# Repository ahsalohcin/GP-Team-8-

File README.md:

# Grand PrIEEE (senior year of undergrad, 2016-2017)

Led a team of 5 for IEEE-sponsored competition for designing a line-following RC car from scratch.

## Competition videos: 
* UC San Diego (3rd place): https://www.youtube.com/watch?v=oybaJ443wYY 
* UC Davis (4th place):  https://www.youtube.com/watch?v=VBZ95nvLsOQ& 

## Overview: 
* 1/12 scale RC car + custom PCB
* __Microcontroller__: Teensy (Arduino based)
* __Sensors__: line camera and hall effect speed sensor
* __Actuators__: servo and brushed DC motor (with custom designed motor driver circuit)
* __Controllers__: PD for steering, PI for speed

## Skills learned: 
* Project management
* Design and integration (mechanical, electrical, and software)
* PCB layout
* Control design and tuning

## Main code: 
https://github.com/ahsalohcin/GP-Team-8-/blob/master/Code_5_7/GP_teensy/GP_teensy.ino

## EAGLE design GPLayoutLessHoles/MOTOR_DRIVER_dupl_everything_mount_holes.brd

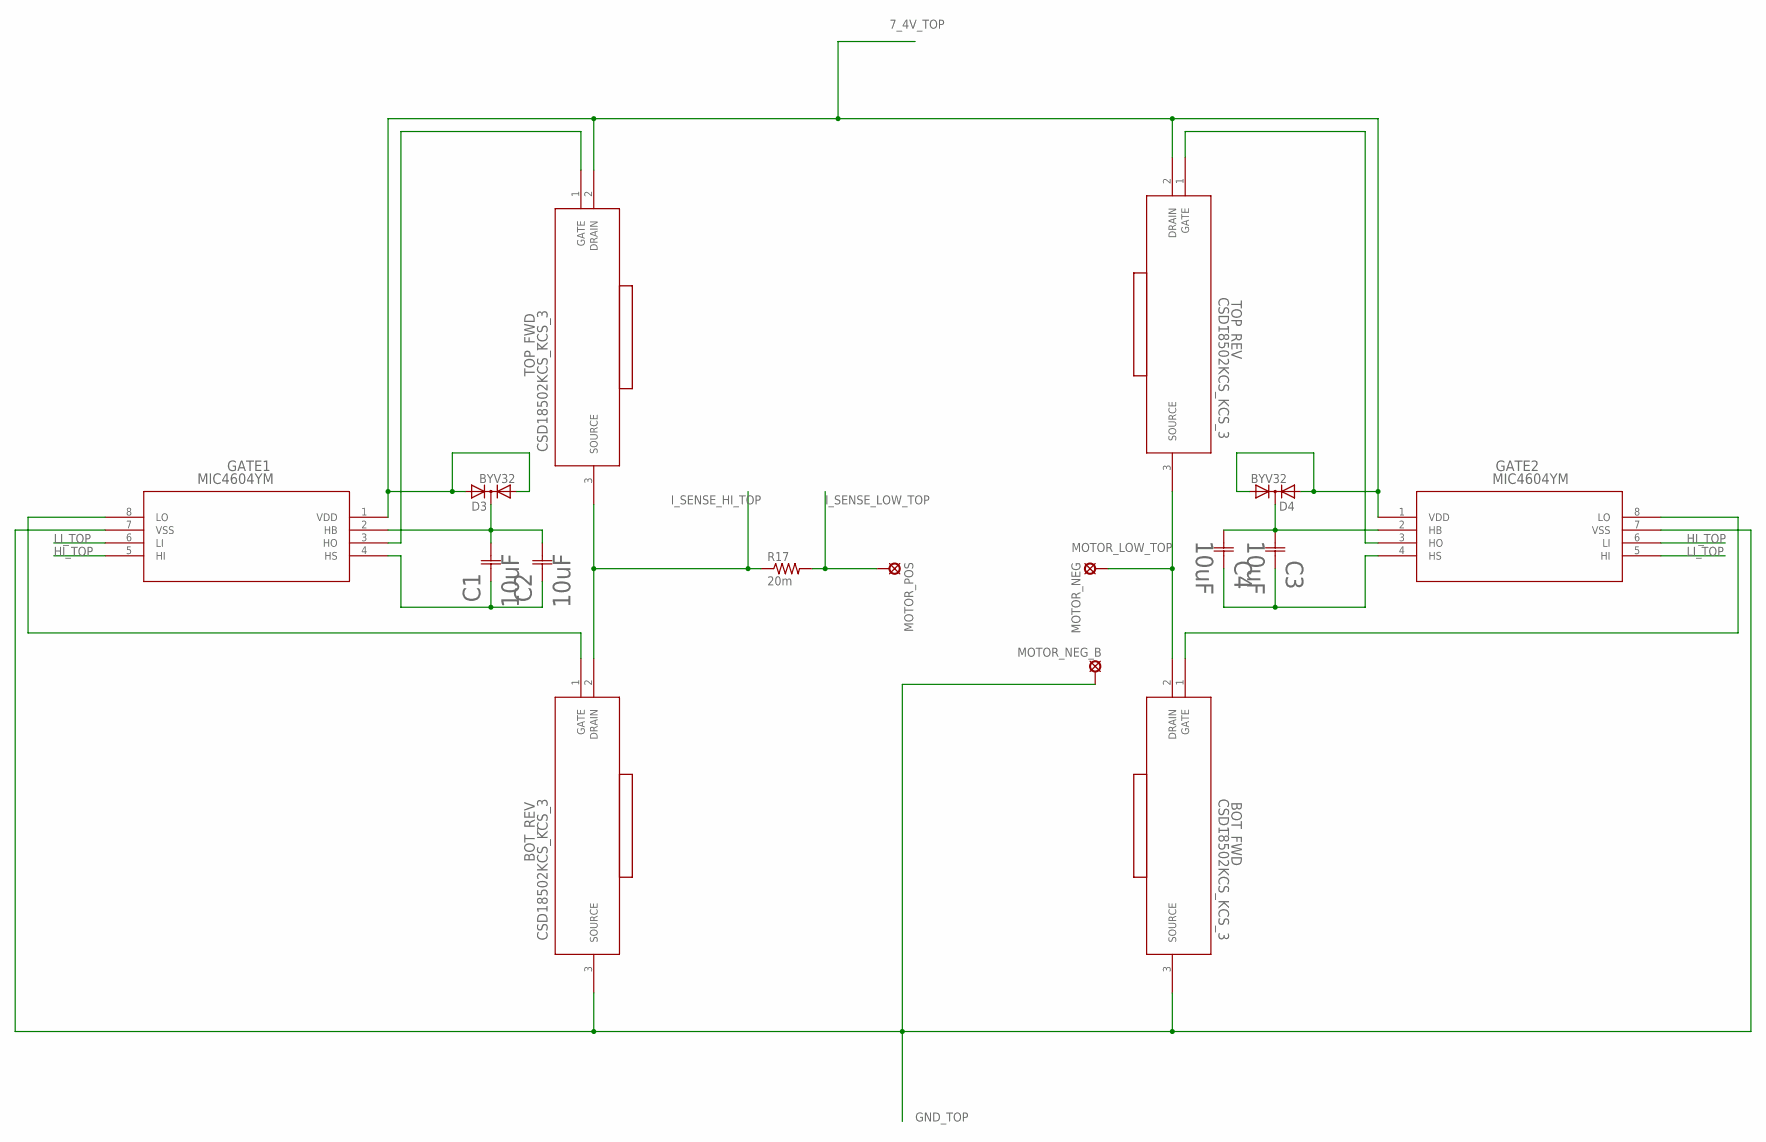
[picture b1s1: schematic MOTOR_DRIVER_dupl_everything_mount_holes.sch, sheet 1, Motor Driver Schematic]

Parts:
BOT_FWD: CSD18502KCS_KCS_3; KCS3
BOT_REV: CSD18502KCS_KCS_3; KCS3
C1, C2, C3, C4: 10uF; CAP_EEE_B
D3, D4: BYV32; TO220ABS
GATE1, GATE2: MIC4604YM; SOIC-8_M
MOTOR_NEG: SE14
MOTOR_NEG_B: SE14
MOTOR_POS: SE14
R17: 20m; R2512
TOP_FWD: CSD18502KCS_KCS_3; KCS3
TOP_REV: CSD18502KCS_KCS_3; KCS3
U$2, U$4, U$5, U$6: HEATSINK

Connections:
7_4V_TOP: D3.A1, D3.A2, D4.A1, D4.A2, GATE1.1 (VDD), GATE2.1 (VDD), TOP_FWD.2 (DRAIN), TOP_REV.2 (DRAIN); also elsewhere on the board
GND_TOP: BOT_FWD.3 (SOURCE), BOT_REV.3 (SOURCE), GATE1.7 (VSS), GATE2.7 (VSS), MOTOR_NEG_B.MP; also elsewhere on the board
HI_TOP: GATE1.5 (HI), GATE2.6 (LI); also elsewhere on the board
I_SENSE_HI_TOP: BOT_REV.2 (DRAIN), R17.1, TOP_FWD.3 (SOURCE); also elsewhere on the board
I_SENSE_LOW_TOP: MOTOR_POS.MP, R17.2; also elsewhere on the board
LI_TOP: GATE1.6 (LI), GATE2.5 (HI); also elsewhere on the board
MOTOR_LOW_TOP: BOT_FWD.2 (DRAIN), MOTOR_NEG.MP, TOP_REV.3 (SOURCE); also elsewhere on the board
unnamed: BOT_REV.1 (GATE), GATE1.8 (LO)
unnamed: GATE1.3 (HO), TOP_FWD.1 (GATE)
unnamed: C1.1, C2.1, GATE1.4 (HS)
unnamed: C1.2, C2.2, D3.C, GATE1.2 (HB)
unnamed: BOT_FWD.1 (GATE), GATE2.8 (LO)
unnamed: GATE2.3 (HO), TOP_REV.1 (GATE)
unnamed: C3.1, C4.1, GATE2.4 (HS)
unnamed: C3.2, C4.2, D4.C, GATE2.2 (HB)

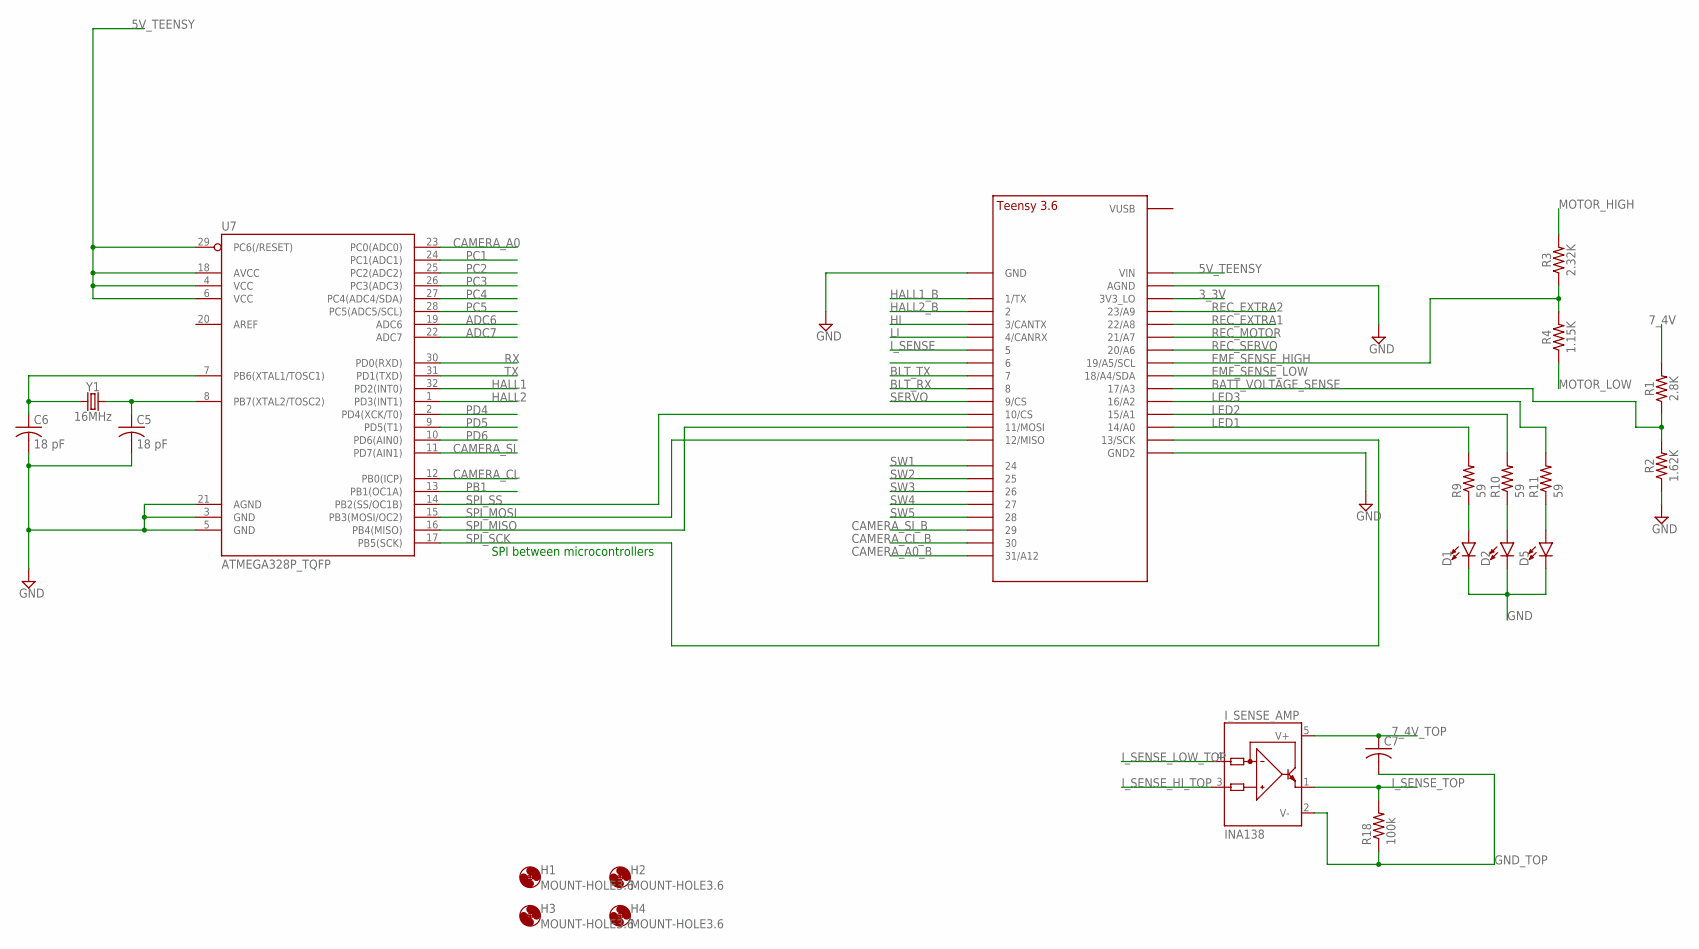
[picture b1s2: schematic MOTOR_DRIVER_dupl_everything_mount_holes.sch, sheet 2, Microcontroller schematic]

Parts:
C5, C6: 18 pF; C0603
C7: C-USC0603; C0603
D1, D2, D5: LED0603; LED-0603
H1, H2, H3, H4: MOUNT-HOLE3.6; 3,6
I_SENSE_AMP: INA138; SOT23-5
R1: 2.8K; 0805; MANUFACTURER_PART_NUMBER RC0805FR-072K8L; DIGIKEY_PART_NUMBER 311-2.80KCRCT-ND
R2: 1.62K; 0805; MANUFACTURER_PART_NUMBER RC0805FR-071K62L; DIGIKEY_PART_NUMBER 311-1.62KCRCT-ND
R3: 2.32K; 0805; MANUFACTURER_PART_NUMBER RC0805FR-072K32L; DIGIKEY_PART_NUMBER 311-2.32KCRCT-ND
R4: 1.15K; 0805; MANUFACTURER_PART_NUMBER RC0805FR-071K15L; DIGIKEY_PART_NUMBER 311-1.15KCRCT-ND
R9, R10, R11: 59; R0805
R18: 100k; R0603
U7: ATMEGA328P_TQFP; TQFP32-08; MANUFACTURER_PART_NUMBER ATMEGA328PB-AU; DIGIKEY_PART_NUMBER ATMEGA328PB-AU-ND
U$1: TEENSY_3.5/3.6_FEWER; TEENSY_3.5/3.6_BASIC_FEWER_PIN; MANUFACTURER_PART_NUMBER DEV-14055; DIGIKEY_PART_NUMBER 1568-1443-ND
Y1: 16MHz; HC49US; MANUFACTURER_PART_NUMBER 9C-16.000MBBK-T; DIGIKEY_PART_NUMBER 887-2425-1-ND

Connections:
3_3V: U$1.3V3_LO; also elsewhere on the board
5V_TEENSY: U7.4 (VCC), U7.6 (VCC), U7.18 (AVCC), U7.29 (PC6(/RESET)), U$1.VIN; also elsewhere on the board
7_4V: R1.2; also elsewhere on the board
7_4V_TOP: C7.1, I_SENSE_AMP.5 (V+); also elsewhere on the board
ADC6: U7.19 (ADC6); also elsewhere on the board
ADC7: U7.22 (ADC7); also elsewhere on the board
BATT_VOLTAGE_SENSE: R1.1, R2.2, U$1.17/A3
BLT_RX: U$1.8; also elsewhere on the board
BLT_TX: U$1.7; also elsewhere on the board
CAMERA_A0: U7.23 (PC0(ADC0)); also elsewhere on the board
CAMERA_A0_B: U$1.31/A12; also elsewhere on the board
CAMERA_CL: U7.12 (PB0(ICP)); also elsewhere on the board
CAMERA_CL_B: U$1.30; also elsewhere on the board
CAMERA_SI: U7.11 (PD7(AIN1)); also elsewhere on the board
CAMERA_SI_B: U$1.29; also elsewhere on the board
EMF_SENSE_HIGH: R3.1, R4.2, U$1.19/A5/SCL
EMF_SENSE_LOW: U$1.18/A4/SDA; also elsewhere on the board
GND: C5.2, C6.2, D1.C, D2.C, D5.C, R2.1, U7.3 (GND), U7.5 (GND), U7.21 (AGND), U$1.AGND, U$1.GND, U$1.GND2; also elsewhere on the board
GND_TOP: C7.2, I_SENSE_AMP.2 (V-), R18.1; also elsewhere on the board
HALL1: U7.32 (PD2(INT0)); also elsewhere on the board
HALL1_B: U$1.1/TX; also elsewhere on the board
HALL2: U7.1 (PD3(INT1)); also elsewhere on the board
HALL2_B: U$1.2; also elsewhere on the board
HI: U$1.3/CANTX; also elsewhere on the board
I_SENSE: U$1.5; also elsewhere on the board
I_SENSE_HI_TOP: I_SENSE_AMP.3 (IN+); also elsewhere on the board
I_SENSE_LOW_TOP: I_SENSE_AMP.4 (IN-); also elsewhere on the board
I_SENSE_TOP: I_SENSE_AMP.1 (OUT), R18.2; also elsewhere on the board
LED1: R9.2, U$1.14/A0
LED2: R10.2, U$1.15/A1
LED3: R11.2, U$1.16/A2
LI: U$1.4/CANRX; also elsewhere on the board
LI2: U$1.6
MOTOR_HIGH: R3.2; also elsewhere on the board
MOTOR_LOW: R4.1; also elsewhere on the board
unnamed: C6.1, U7.7 (PB6(XTAL1/TOSC1)), Y1.1
unnamed: C5.1, U7.8 (PB7(XTAL2/TOSC2)), Y1.2
unnamed: D1.A, R9.1
unnamed: D2.A, R10.1
unnamed: D5.A, R11.1
PB1: U7.13 (PB1(OC1A)); also elsewhere on the board
PC1: U7.24 (PC1(ADC1)); also elsewhere on the board
PC2: U7.25 (PC2(ADC2)); also elsewhere on the board
PC3: U7.26 (PC3(ADC3)); also elsewhere on the board
PC4: U7.27 (PC4(ADC4/SDA)); also elsewhere on the board
PC5: U7.28 (PC5(ADC5/SCL)); also elsewhere on the board
PD4: U7.2 (PD4(XCK/T0)); also elsewhere on the board
PD5: U7.9 (PD5(T1)); also elsewhere on the board
PD6: U7.10 (PD6(AIN0))
REC_EXTRA1: U$1.22/A8; also elsewhere on the board
REC_EXTRA2: U$1.23/A9; also elsewhere on the board
REC_MOTOR: U$1.21/A7; also elsewhere on the board
REC_SERVO: U$1.20/A6; also elsewhere on the board
RX: U7.30 (PD0(RXD)); also elsewhere on the board
SERVO: U$1.9/CS; also elsewhere on the board
SPI_MISO: U7.16 (PB4(MISO)), U$1.11/MOSI
SPI_MOSI: U7.15 (PB3(MOSI/OC2)), U$1.12/MISO
SPI_SCK: U7.17 (PB5(SCK)), U$1.13/SCK
SPI_SS: U7.14 (PB2(SS/OC1B)), U$1.10/CS
SW1: U$1.24; also elsewhere on the board
SW2: U$1.25; also elsewhere on the board
SW3: U$1.26; also elsewhere on the board
SW4: U$1.27; also elsewhere on the board
SW5: U$1.28
TX: U7.31 (PD1(TXD)); also elsewhere on the board

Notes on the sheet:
SPI between microcontrollers

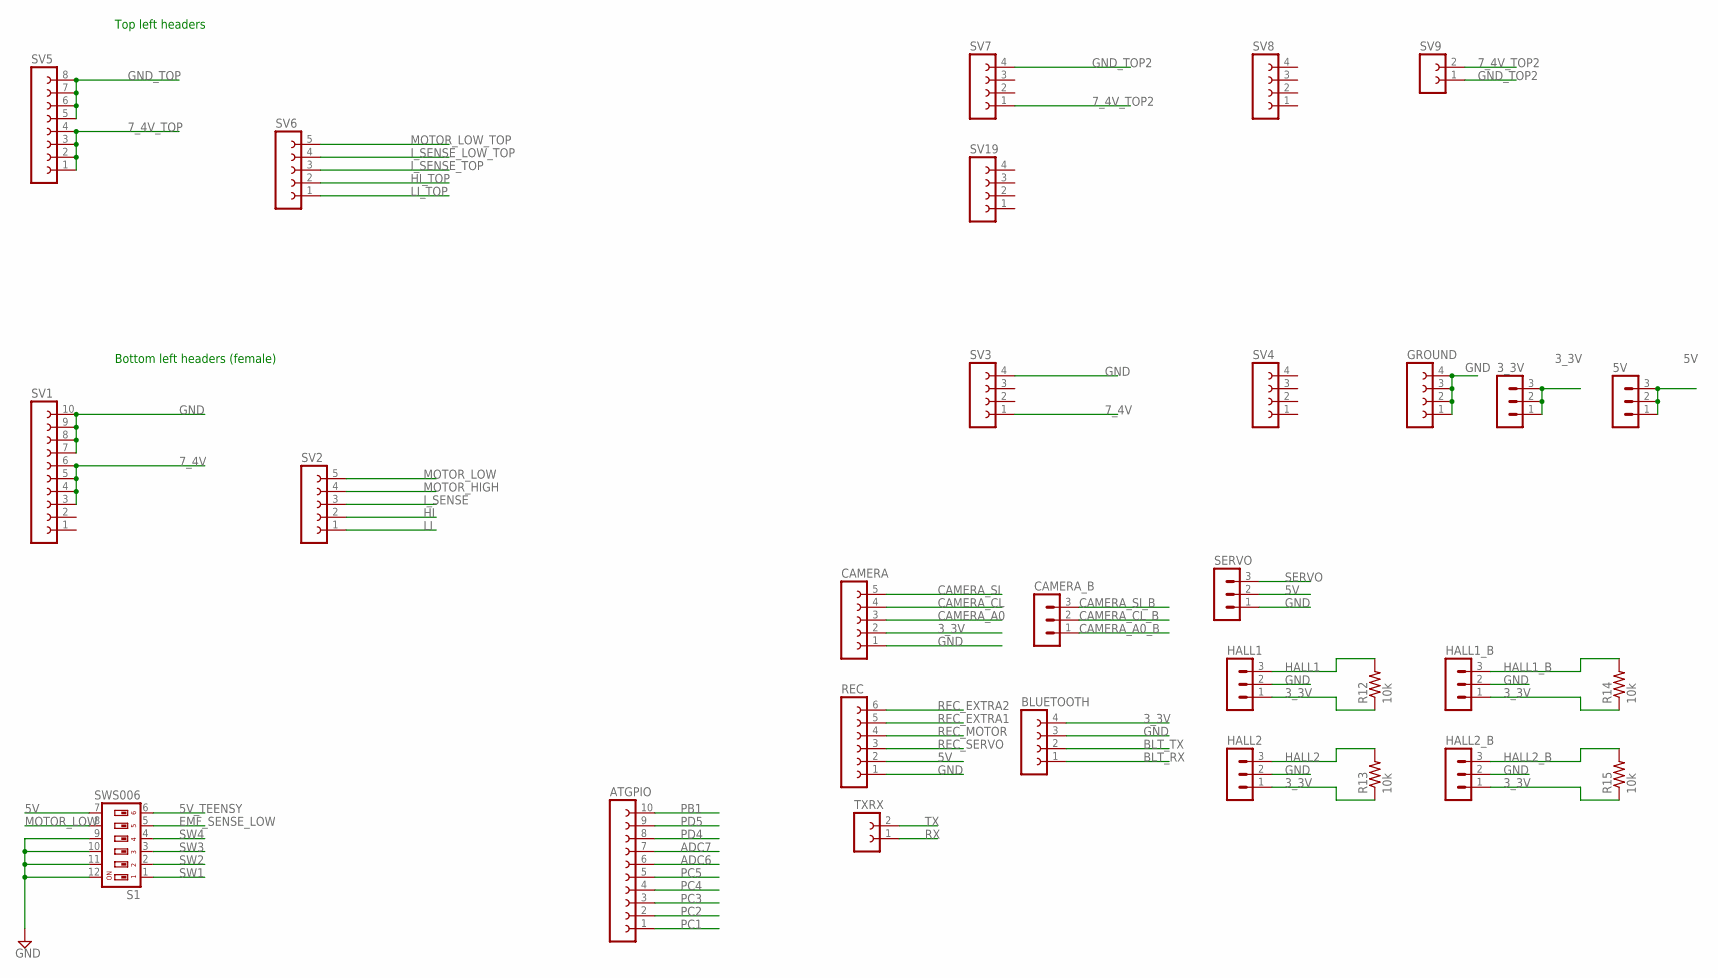
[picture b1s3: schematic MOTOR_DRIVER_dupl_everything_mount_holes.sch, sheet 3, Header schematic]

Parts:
3_3V, 5V: MA03-1
ATGPIO: FE10-1; FE10
BLUETOOTH: FE04-1; MANUFACTURER_PART_NUMBER HC-06
CAMERA: FE05-1; MANUFACTURER_PART_NUMBER 28317; DIGIKEY_PART_NUMBER 28317-ND
CAMERA_B: MA03-1; MANUFACTURER_PART_NUMBER 28317; DIGIKEY_PART_NUMBER 28317-ND
GROUND: FE04-1
HALL1, HALL1_B, HALL2, HALL2_B: MA03-1; MANUFACTURER_PART_NUMBER US1881LUA-AAA-000-BU; DIGIKEY_PART_NUMBER US1881LUA-AAA-000-BU-ND
R12, R13, R14, R15: 10k; R0603
REC: FE06-1; FE06
S1: SWS006; SMS-006; MANUFACTURER_PART_NUMBER 219-6MST; DIGIKEY_PART_NUMBER CT2196MST-ND
SERVO: MA03-1; MANUFACTURER_PART_NUMBER TS-P12S
SV1: FE10-1; FE10
SV2, SV6: FE05-1
SV3, SV4, SV7, SV8, SV19: FE04-1
SV5: FE08-1; FE08
SV9: FE02-1
TXRX: FE02-1

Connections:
3_3V: 3_3V.1, 3_3V.2, 3_3V.3, BLUETOOTH.4, CAMERA.2, HALL1.1, HALL1_B.1, HALL2.1, HALL2_B.1, R12.1, R13.1, R14.1, R15.1; also elsewhere on the board
5V: 5V.1, 5V.2, 5V.3, REC.2, S1.7, SERVO.2; also elsewhere on the board
5V_TEENSY: S1.6; also elsewhere on the board
7_4V: SV1.3, SV1.4, SV1.5, SV1.6, SV3.1; also elsewhere on the board
7_4V_TOP: SV5.1, SV5.2, SV5.3, SV5.4; also elsewhere on the board
7_4V_TOP2: SV7.1, SV9.2; also elsewhere on the board
ADC6: ATGPIO.6; also elsewhere on the board
ADC7: ATGPIO.7; also elsewhere on the board
BLT_RX: BLUETOOTH.1; also elsewhere on the board
BLT_TX: BLUETOOTH.2; also elsewhere on the board
CAMERA_A0: CAMERA.3; also elsewhere on the board
CAMERA_A0_B: CAMERA_B.1; also elsewhere on the board
CAMERA_CL: CAMERA.4; also elsewhere on the board
CAMERA_CL_B: CAMERA_B.2; also elsewhere on the board
CAMERA_SI: CAMERA.5; also elsewhere on the board
CAMERA_SI_B: CAMERA_B.3; also elsewhere on the board
EMF_SENSE_LOW: S1.5; also elsewhere on the board
GND: BLUETOOTH.3, CAMERA.1, GROUND.1, GROUND.2, GROUND.3, GROUND.4, HALL1.2, HALL1_B.2, HALL2.2, HALL2_B.2, REC.1, S1.9, S1.10, S1.11, S1.12, SERVO.1, SV1.7, SV1.8, SV1.9, SV1.10, SV3.4; also elsewhere on the board
GND_TOP: SV5.5, SV5.6, SV5.7, SV5.8; also elsewhere on the board
GND_TOP2: SV7.4, SV9.1; also elsewhere on the board
HALL1: HALL1.3, R12.2; also elsewhere on the board
HALL1_B: HALL1_B.3, R14.2; also elsewhere on the board
HALL2: HALL2.3, R13.2; also elsewhere on the board
HALL2_B: HALL2_B.3, R15.2; also elsewhere on the board
HI: SV2.2; also elsewhere on the board
HI_TOP: SV6.2; also elsewhere on the board
I_SENSE: SV2.3; also elsewhere on the board
I_SENSE_LOW_TOP: SV6.4; also elsewhere on the board
I_SENSE_TOP: SV6.3; also elsewhere on the board
LI: SV2.1; also elsewhere on the board
LI_TOP: SV6.1; also elsewhere on the board
MOTOR_HIGH: SV2.4; also elsewhere on the board
MOTOR_LOW: S1.8, SV2.5; also elsewhere on the board
MOTOR_LOW_TOP: SV6.5; also elsewhere on the board
PB1: ATGPIO.10; also elsewhere on the board
PC1: ATGPIO.1; also elsewhere on the board
PC2: ATGPIO.2; also elsewhere on the board
PC3: ATGPIO.3; also elsewhere on the board
PC4: ATGPIO.4; also elsewhere on the board
PC5: ATGPIO.5; also elsewhere on the board
PD4: ATGPIO.8; also elsewhere on the board
PD5: ATGPIO.9; also elsewhere on the board
REC_EXTRA1: REC.5; also elsewhere on the board
REC_EXTRA2: REC.6; also elsewhere on the board
REC_MOTOR: REC.4; also elsewhere on the board
REC_SERVO: REC.3; also elsewhere on the board
RX: TXRX.1; also elsewhere on the board
SERVO: SERVO.3; also elsewhere on the board
SW1: S1.1; also elsewhere on the board
SW2: S1.2; also elsewhere on the board
SW3: S1.3; also elsewhere on the board
SW4: S1.4; also elsewhere on the board
TX: TXRX.2; also elsewhere on the board

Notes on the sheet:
Bottom left headers (female)
Top left headers

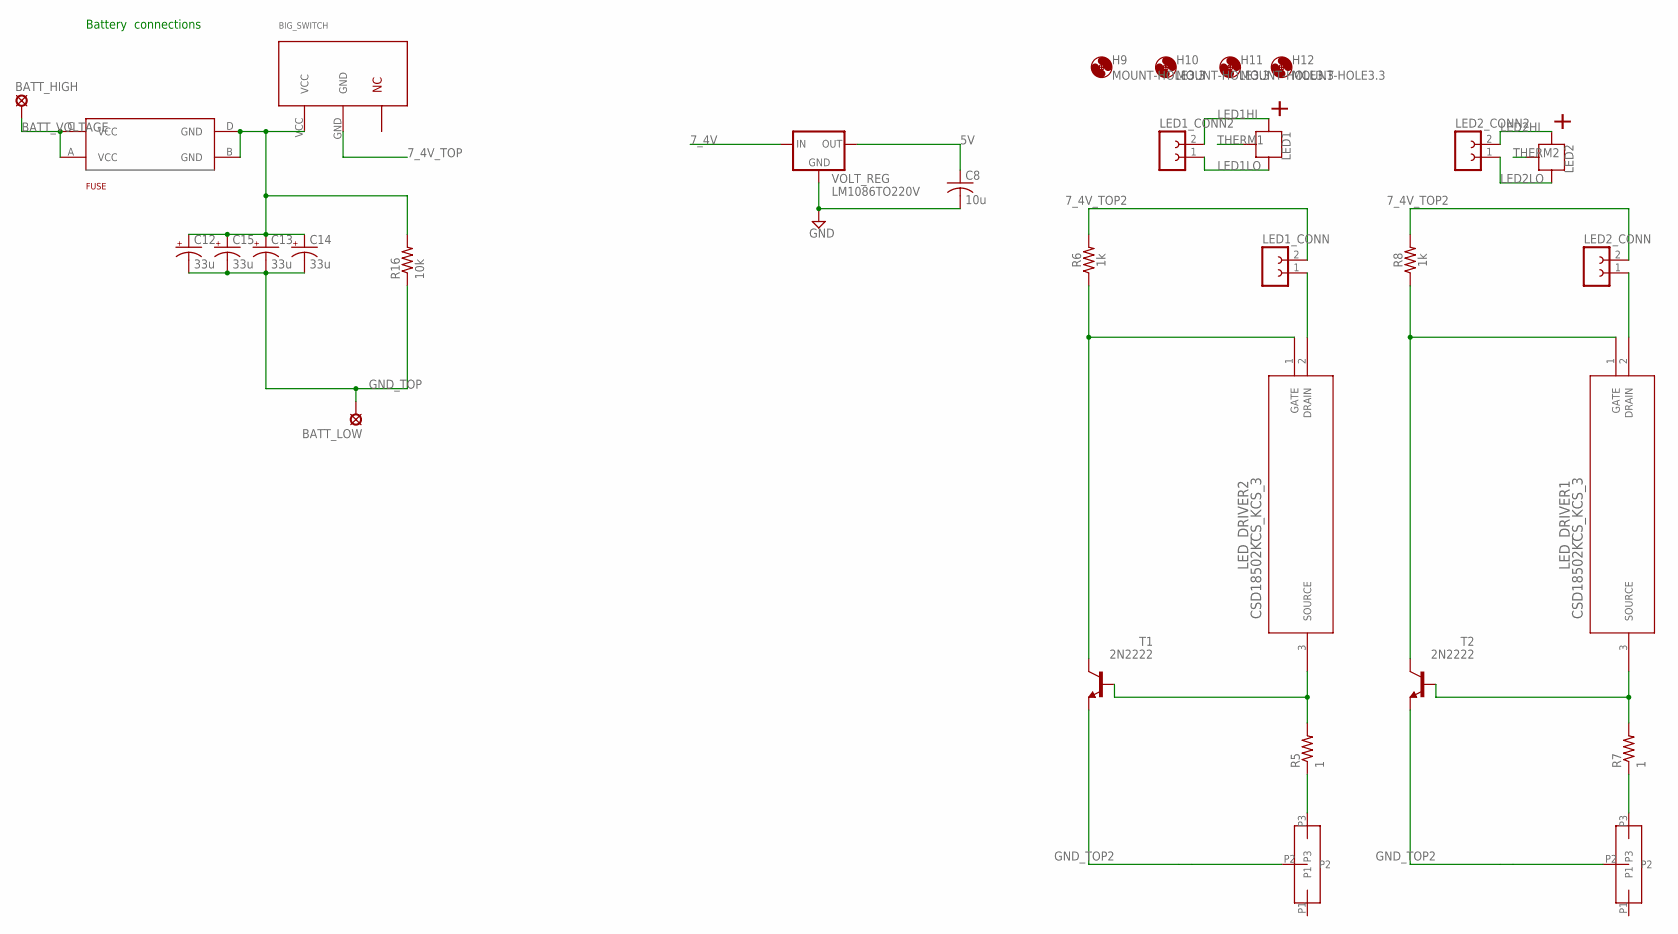
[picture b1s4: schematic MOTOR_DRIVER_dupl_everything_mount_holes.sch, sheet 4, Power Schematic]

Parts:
BATT_HIGH: SE14
BATT_LOW: SE14
BIG_SWITCH: BIGSWITCH; MANUFACTURER_PART_NUMBER GRB238B801BR1; DIGIKEY_PART_NUMBER CW106-ND
C8: 10u; C0805
C12, C13, C14, C15: 33u; 153CLV-1010
FUSE: FUSEHOLDER3588; MANUFACTURER_PART_NUMBER 0891010.NXS; DIGIKEY_PART_NUMBER F4989-ND
H9, H10, H11, H12: MOUNT-HOLE3.3; 3,3
LED1, LED2: CREE_XP; XP
LED1_CONN, LED1_CONN2, LED2_CONN, LED2_CONN2: FE02-1
LED_DRIVER1, LED_DRIVER2: CSD18502KCS_KCS_3; KCS3
R5, R7: 1; R2512
R6, R8: 1k; AXIAL-0.3
R16: 10k; R0603
T1, T2: 2N2222; TO18
U$3, U$7: POT
VOLT_REG: LM1086TO220V; TO220S; MANUFACTURER_PART_NUMBER LM1086IT-5.0/NOPB; DIGIKEY_PART_NUMBER LM1086IT-5.0/NOPB-ND

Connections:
5V: C8.1, VOLT_REG.2 (OUT); also elsewhere on the board
7_4V: VOLT_REG.3 (IN); also elsewhere on the board
7_4V_TOP: BIG_SWITCH.GND; also elsewhere on the board
7_4V_TOP2: LED1_CONN.2, LED2_CONN.2, R6.P$2 (2), R8.P$2 (2); also elsewhere on the board
BATT_VOLTAGE: BATT_HIGH.MP, FUSE.A (VCC), FUSE.C (VCC)
GND: C8.2, VOLT_REG.1 (GND); also elsewhere on the board
GND_TOP: BATT_LOW.MP, C12.-, C13.-, C14.-, C15.-, R16.1; also elsewhere on the board
GND_TOP2: T1.1 (E), T2.1 (E), U$3.P2, U$7.P2; also elsewhere on the board
LED1HI: LED1.POSITIVE, LED1.POSITIVE1 (POSITIVE), LED1_CONN2.2
LED1LO: LED1.NEGATIVE, LED1.NEGATIVE1 (NEGATIVE), LED1_CONN2.1
LED2HI: LED2.POSITIVE, LED2.POSITIVE1 (POSITIVE), LED2_CONN2.2
LED2LO: LED2.NEGATIVE, LED2.NEGATIVE1 (NEGATIVE), LED2_CONN2.1
unnamed: R5.1, U$7.P3
unnamed: LED_DRIVER2.3 (SOURCE), R5.2, T1.2 (B)
unnamed: R7.1, U$3.P3
unnamed: LED_DRIVER2.1 (GATE), R6.P$1 (1), T1.3 (C)
unnamed: LED1_CONN.1, LED_DRIVER2.2 (DRAIN)
unnamed: LED_DRIVER1.3 (SOURCE), R7.2, T2.2 (B)
unnamed: LED_DRIVER1.1 (GATE), R8.P$1 (1), T2.3 (C)
unnamed: LED2_CONN.1, LED_DRIVER1.2 (DRAIN)
unnamed: BIG_SWITCH.VCC, C12.+, C13.+, C14.+, C15.+, FUSE.B (GND), FUSE.D (GND), R16.2
THERM1: LED1.THERMAL
THERM2: LED2.THERMAL

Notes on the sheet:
Battery connections

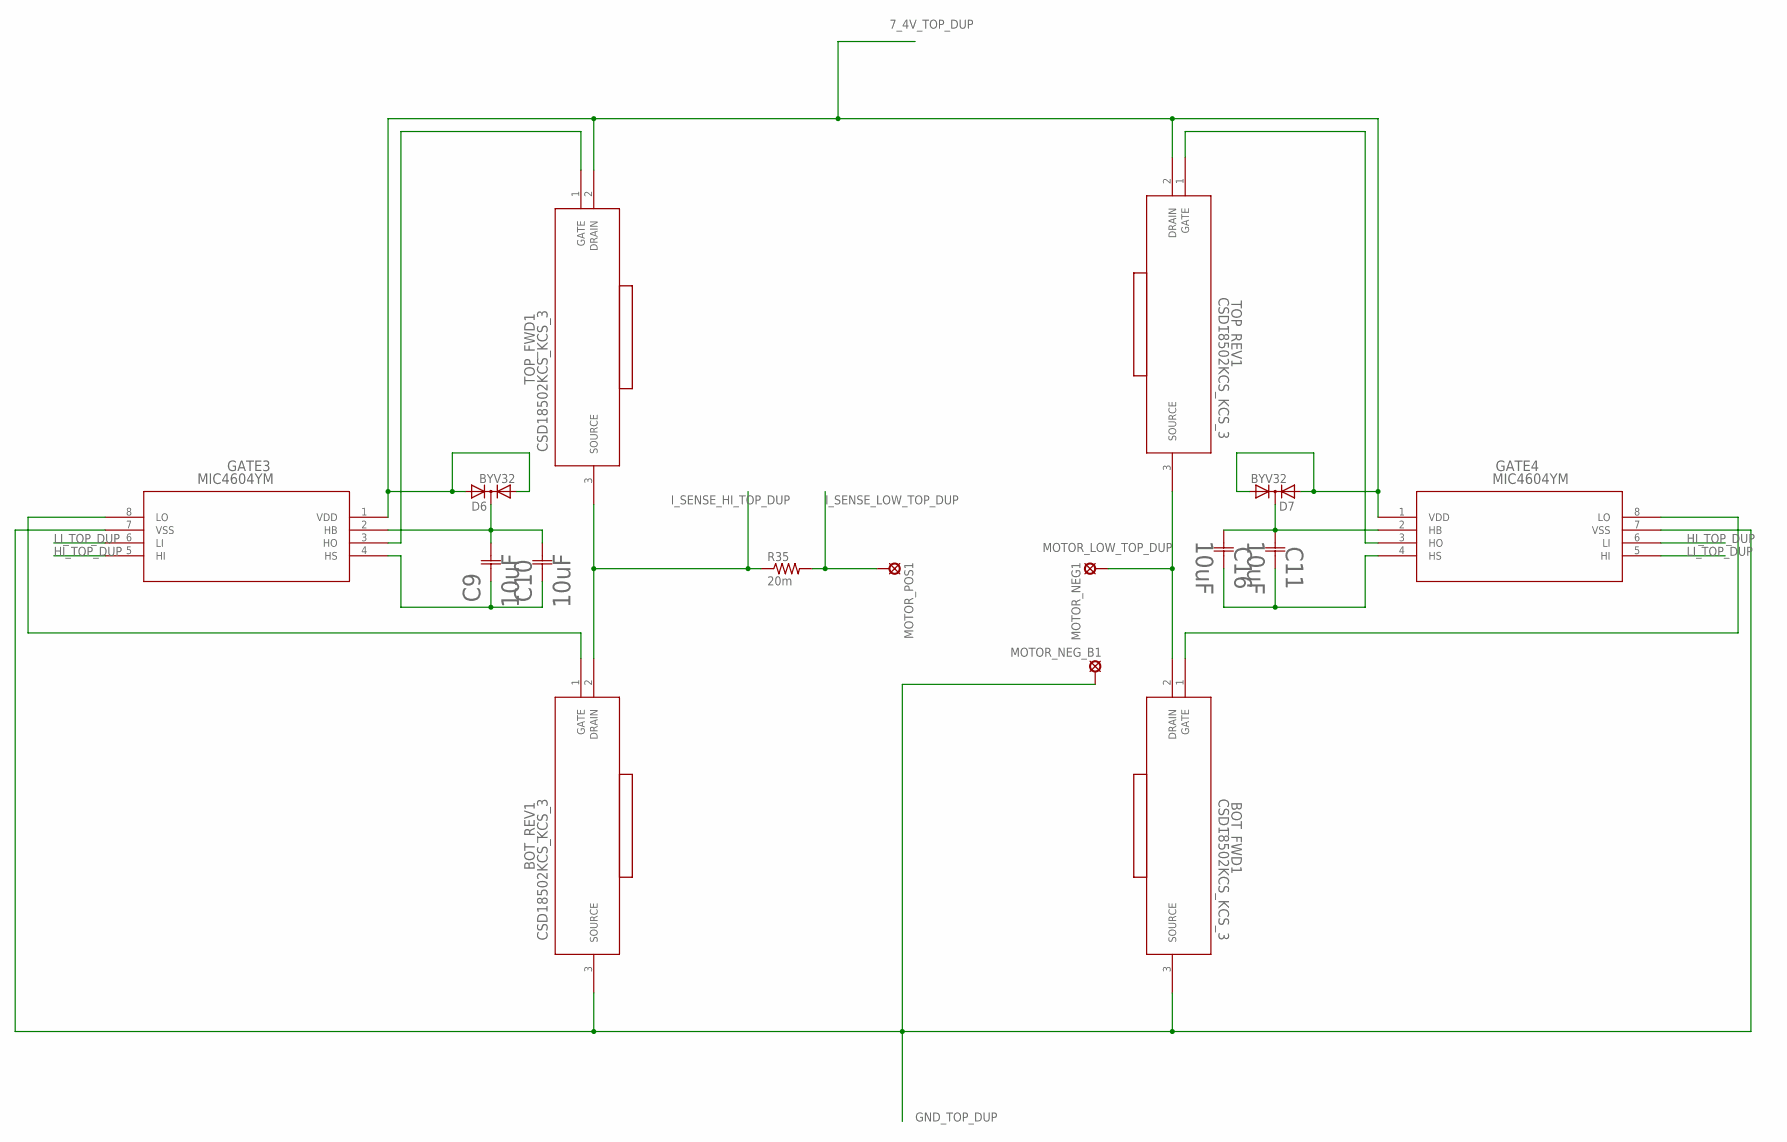
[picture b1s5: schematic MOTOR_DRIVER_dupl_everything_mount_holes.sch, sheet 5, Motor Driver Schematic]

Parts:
BOT_FWD1: CSD18502KCS_KCS_3; KCS3
BOT_REV1: CSD18502KCS_KCS_3; KCS3
C9, C10, C11, C16: 10uF; CAP_EEE_B
D6, D7: BYV32; TO220ABS
GATE3, GATE4: MIC4604YM; SOIC-8_M
MOTOR_NEG1: SE14
MOTOR_NEG_B1: SE14
MOTOR_POS1: SE14
R35: 20m; R2512
TOP_FWD1: CSD18502KCS_KCS_3; KCS3
TOP_REV1: CSD18502KCS_KCS_3; KCS3
U$10, U$11, U$12, U$13: HEATSINK

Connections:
7_4V_TOP_DUP: D6.A1, D6.A2, D7.A1, D7.A2, GATE3.1 (VDD), GATE4.1 (VDD), TOP_FWD1.2 (DRAIN), TOP_REV1.2 (DRAIN); also elsewhere on the board
GND_TOP_DUP: BOT_FWD1.3 (SOURCE), BOT_REV1.3 (SOURCE), GATE3.7 (VSS), GATE4.7 (VSS), MOTOR_NEG_B1.MP; also elsewhere on the board
HI_TOP_DUP: GATE3.5 (HI), GATE4.6 (LI); also elsewhere on the board
I_SENSE_HI_TOP_DUP: BOT_REV1.2 (DRAIN), R35.1, TOP_FWD1.3 (SOURCE); also elsewhere on the board
I_SENSE_LOW_TOP_DUP: MOTOR_POS1.MP, R35.2; also elsewhere on the board
LI_TOP_DUP: GATE3.6 (LI), GATE4.5 (HI); also elsewhere on the board
MOTOR_LOW_TOP_DUP: BOT_FWD1.2 (DRAIN), MOTOR_NEG1.MP, TOP_REV1.3 (SOURCE); also elsewhere on the board
unnamed: BOT_REV1.1 (GATE), GATE3.8 (LO)
unnamed: GATE3.3 (HO), TOP_FWD1.1 (GATE)
unnamed: C9.1, C10.1, GATE3.4 (HS)
unnamed: C9.2, C10.2, D6.C, GATE3.2 (HB)
unnamed: BOT_FWD1.1 (GATE), GATE4.8 (LO)
unnamed: GATE4.3 (HO), TOP_REV1.1 (GATE)
unnamed: C11.1, C16.1, GATE4.4 (HS)
unnamed: C11.2, C16.2, D7.C, GATE4.2 (HB)

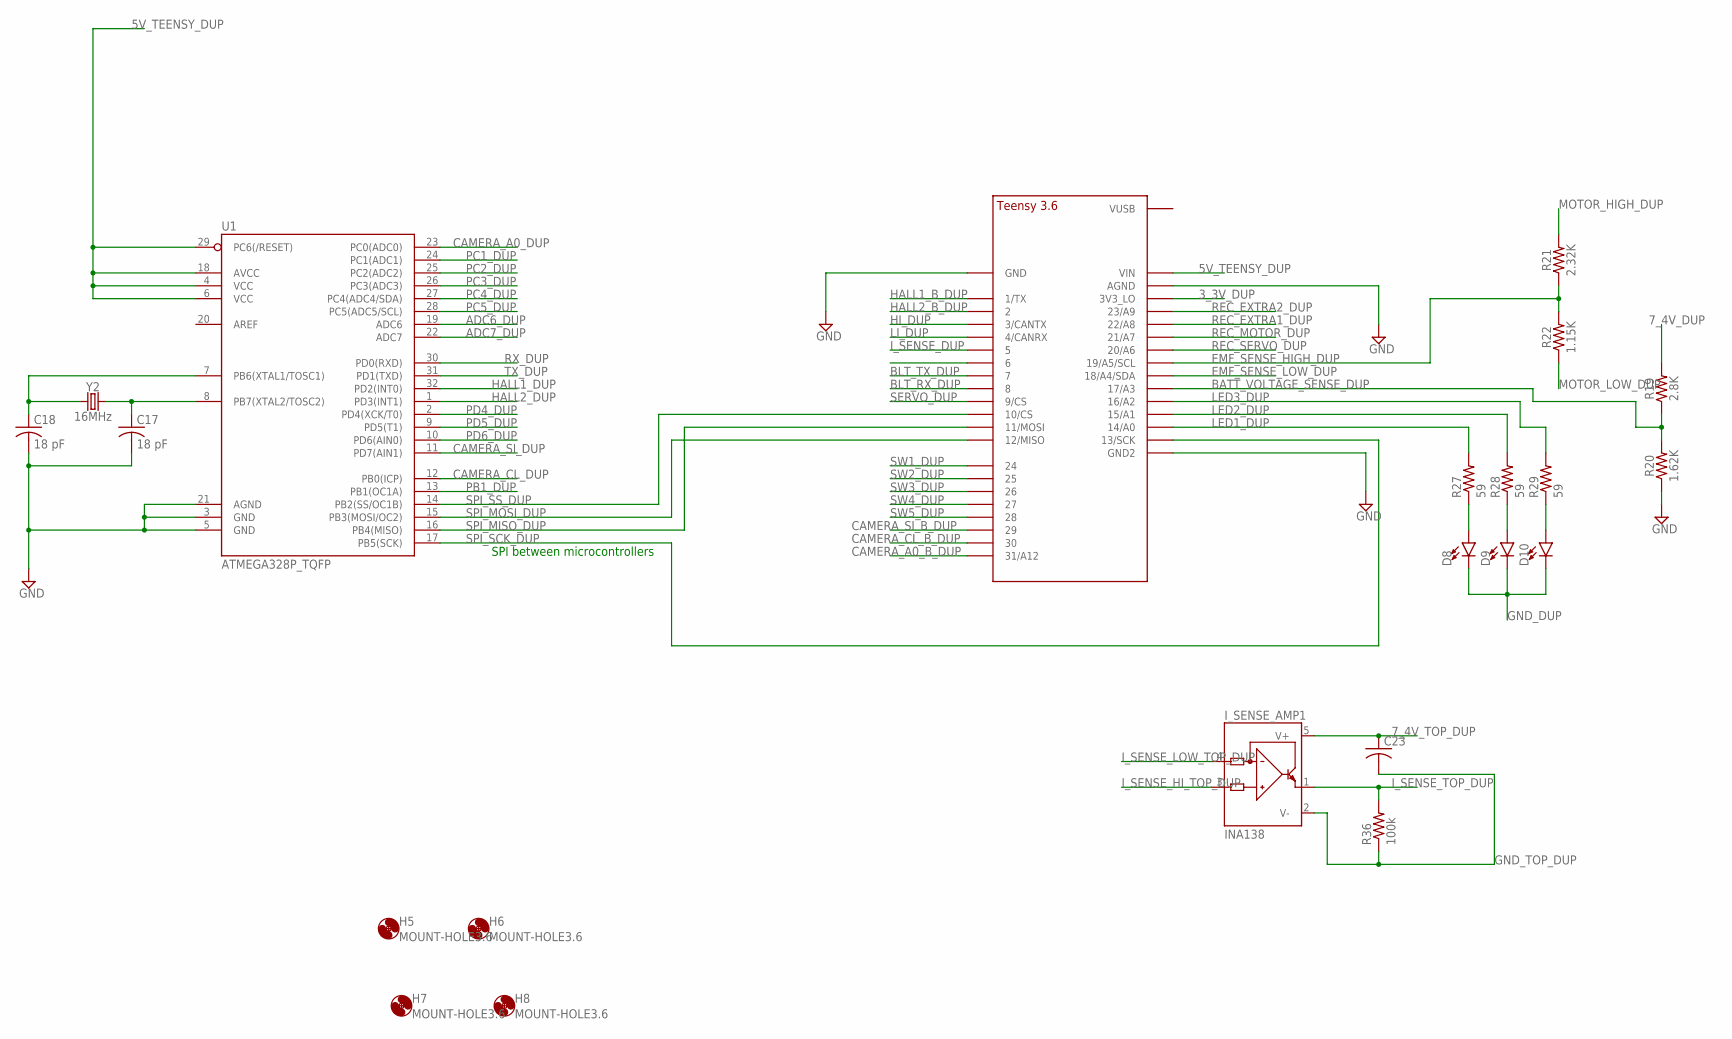
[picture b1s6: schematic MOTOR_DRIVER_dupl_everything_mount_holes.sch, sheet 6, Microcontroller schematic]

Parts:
C17, C18: 18 pF; C0603
C23: C-USC0603; C0603
D8, D9, D10: LED0603; LED-0603
H5, H6, H7, H8: MOUNT-HOLE3.6; 3,6
I_SENSE_AMP1: INA138; SOT23-5
R19: 2.8K; 0805; MANUFACTURER_PART_NUMBER RC0805FR-072K8L; DIGIKEY_PART_NUMBER 311-2.80KCRCT-ND
R20: 1.62K; 0805; MANUFACTURER_PART_NUMBER RC0805FR-071K62L; DIGIKEY_PART_NUMBER 311-1.62KCRCT-ND
R21: 2.32K; 0805; MANUFACTURER_PART_NUMBER RC0805FR-072K32L; DIGIKEY_PART_NUMBER 311-2.32KCRCT-ND
R22: 1.15K; 0805; MANUFACTURER_PART_NUMBER RC0805FR-071K15L; DIGIKEY_PART_NUMBER 311-1.15KCRCT-ND
R27, R28, R29: 59; R0805
R36: 100k; R0603
U1: ATMEGA328P_TQFP; TQFP32-08; MANUFACTURER_PART_NUMBER ATMEGA328PB-AU; DIGIKEY_PART_NUMBER ATMEGA328PB-AU-ND
U$9: TEENSY_3.5/3.6_FEWER; TEENSY_3.5/3.6_BASIC_FEWER_PIN; MANUFACTURER_PART_NUMBER DEV-14055; DIGIKEY_PART_NUMBER 1568-1443-ND
Y2: 16MHz; HC49US; MANUFACTURER_PART_NUMBER 9C-16.000MBBK-T; DIGIKEY_PART_NUMBER 887-2425-1-ND

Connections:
3_3V_DUP: U$9.3V3_LO; also elsewhere on the board
5V_TEENSY_DUP: U1.4 (VCC), U1.6 (VCC), U1.18 (AVCC), U1.29 (PC6(/RESET)), U$9.VIN; also elsewhere on the board
7_4V_DUP: R19.2; also elsewhere on the board
7_4V_TOP_DUP: C23.1, I_SENSE_AMP1.5 (V+); also elsewhere on the board
ADC6_DUP: U1.19 (ADC6); also elsewhere on the board
ADC7_DUP: U1.22 (ADC7); also elsewhere on the board
BATT_VOLTAGE_SENSE_DUP: R19.1, R20.2, U$9.17/A3
BLT_RX_DUP: U$9.8; also elsewhere on the board
BLT_TX_DUP: U$9.7; also elsewhere on the board
CAMERA_A0_B_DUP: U$9.31/A12; also elsewhere on the board
CAMERA_A0_DUP: U1.23 (PC0(ADC0)); also elsewhere on the board
CAMERA_CL_B_DUP: U$9.30; also elsewhere on the board
CAMERA_CL_DUP: U1.12 (PB0(ICP)); also elsewhere on the board
CAMERA_SI_B_DUP: U$9.29; also elsewhere on the board
CAMERA_SI_DUP: U1.11 (PD7(AIN1)); also elsewhere on the board
EMF_SENSE_HIGH_DUP: R21.1, R22.2, U$9.19/A5/SCL
EMF_SENSE_LOW_DUP: U$9.18/A4/SDA; also elsewhere on the board
GND_DUP: C17.2, C18.2, D8.C, D9.C, D10.C, R20.1, U1.3 (GND), U1.5 (GND), U1.21 (AGND), U$9.AGND, U$9.GND, U$9.GND2; also elsewhere on the board
GND_TOP_DUP: C23.2, I_SENSE_AMP1.2 (V-), R36.1; also elsewhere on the board
HALL1_B_DUP: U$9.1/TX; also elsewhere on the board
HALL1_DUP: U1.32 (PD2(INT0)); also elsewhere on the board
HALL2_B_DUP: U$9.2; also elsewhere on the board
HALL2_DUP: U1.1 (PD3(INT1)); also elsewhere on the board
HI_DUP: U$9.3/CANTX; also elsewhere on the board
I_SENSE_DUP: U$9.5; also elsewhere on the board
I_SENSE_HI_TOP_DUP: I_SENSE_AMP1.3 (IN+); also elsewhere on the board
I_SENSE_LOW_TOP_DUP: I_SENSE_AMP1.4 (IN-); also elsewhere on the board
I_SENSE_TOP_DUP: I_SENSE_AMP1.1 (OUT), R36.2; also elsewhere on the board
LED1_DUP: R27.2, U$9.14/A0
LED2_DUP: R28.2, U$9.15/A1
LED3_DUP: R29.2, U$9.16/A2
LI2_DUP: U$9.6
LI_DUP: U$9.4/CANRX; also elsewhere on the board
MOTOR_HIGH_DUP: R21.2; also elsewhere on the board
MOTOR_LOW_DUP: R22.1; also elsewhere on the board
unnamed: C18.1, U1.7 (PB6(XTAL1/TOSC1)), Y2.1
unnamed: C17.1, U1.8 (PB7(XTAL2/TOSC2)), Y2.2
unnamed: D8.A, R27.1
unnamed: D9.A, R28.1
unnamed: D10.A, R29.1
PB1_DUP: U1.13 (PB1(OC1A)); also elsewhere on the board
PC1_DUP: U1.24 (PC1(ADC1)); also elsewhere on the board
PC2_DUP: U1.25 (PC2(ADC2)); also elsewhere on the board
PC3_DUP: U1.26 (PC3(ADC3)); also elsewhere on the board
PC4_DUP: U1.27 (PC4(ADC4/SDA)); also elsewhere on the board
PC5_DUP: U1.28 (PC5(ADC5/SCL)); also elsewhere on the board
PD4_DUP: U1.2 (PD4(XCK/T0)); also elsewhere on the board
PD5_DUP: U1.9 (PD5(T1)); also elsewhere on the board
PD6_DUP: U1.10 (PD6(AIN0))
REC_EXTRA1_DUP: U$9.22/A8; also elsewhere on the board
REC_EXTRA2_DUP: U$9.23/A9; also elsewhere on the board
REC_MOTOR_DUP: U$9.21/A7; also elsewhere on the board
REC_SERVO_DUP: U$9.20/A6; also elsewhere on the board
RX_DUP: U1.30 (PD0(RXD)); also elsewhere on the board
SERVO_DUP: U$9.9/CS; also elsewhere on the board
SPI_MISO_DUP: U1.16 (PB4(MISO)), U$9.11/MOSI
SPI_MOSI_DUP: U1.15 (PB3(MOSI/OC2)), U$9.12/MISO
SPI_SCK_DUP: U1.17 (PB5(SCK)), U$9.13/SCK
SPI_SS_DUP: U1.14 (PB2(SS/OC1B)), U$9.10/CS
SW1_DUP: U$9.24; also elsewhere on the board
SW2_DUP: U$9.25; also elsewhere on the board
SW3_DUP: U$9.26; also elsewhere on the board
SW4_DUP: U$9.27; also elsewhere on the board
SW5_DUP: U$9.28
TX_DUP: U1.31 (PD1(TXD)); also elsewhere on the board

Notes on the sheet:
SPI between microcontrollers

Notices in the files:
parts and their libraries:
SparkFun-IC-Microcontroller: Licensing: Creative Commons ShareAlike 4.0 International - https://creativecommons.org/licenses/by-sa/4.0
COPYRIGHT: Copyright C 2015 Accelerated Designs. All rights reserved
